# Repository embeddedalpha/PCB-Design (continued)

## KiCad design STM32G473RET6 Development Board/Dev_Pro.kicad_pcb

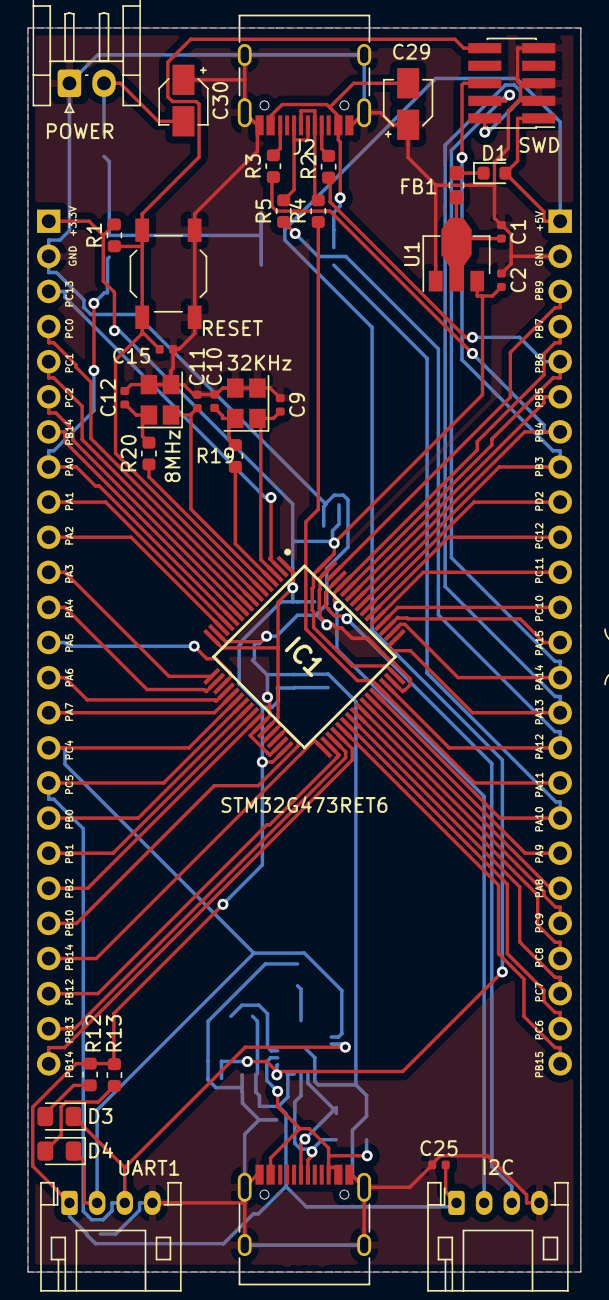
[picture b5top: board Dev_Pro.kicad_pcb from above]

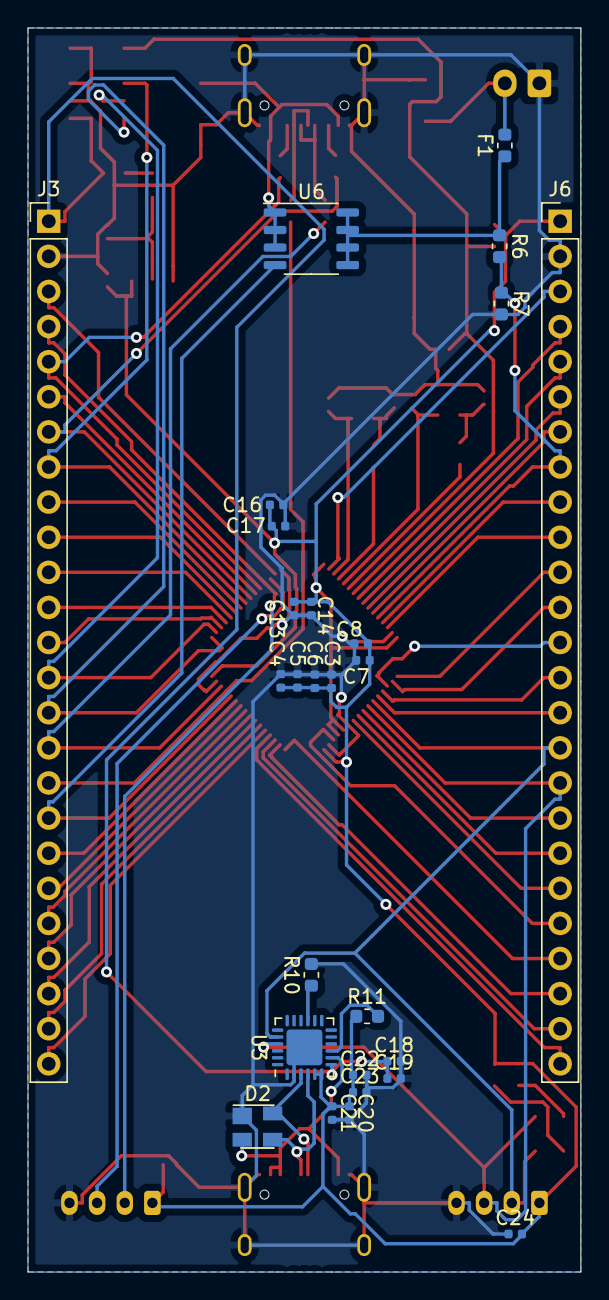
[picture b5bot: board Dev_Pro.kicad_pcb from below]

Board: 2 copper layers, 40.0 x 90.0 mm, 61 parts (27 on the bottom side), 73 nets.

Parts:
8MHz, 32KHz: Crystal_GND23; Crystal_SMD_SeikoEpson_FA238-4Pin_3.2x2.5mm
C1, C2, C24, C25: C_Small; C_0402_1005Metric
C3, C7, C13, C16, C18, C20, C22: 4.7U; C_0402_1005Metric
C4, C5, C6, C8, C9, C10, C11, C12, C14, C15, C17: 100N; C_0402_1005Metric
C19, C21, C23: 0.1U; C_0402_1005Metric
C29, C30: C; CP_Elec_3x5.3
D1: D_Schottky; D_0603_1608Metric
D2: SP0503BAHT; SOT-143
D3, D4: LED; LED_0805_2012Metric_Pad1.15x1.40mm_HandSolder
F1: Fuse; Fuse_0603_1608Metric
FB1: Ferrite_Bead; L_0603_1608Metric_Pad1.05x0.95mm_HandSolder
I2C: Conn_01x04; JST_PH_S4B-PH-K_1x04_P2.00mm_Horizontal
IC1: STM32G473RET6; QFP50P1200X1200X160-64N_STM32G473RET6
J1: Screw_Terminal_01x02; JST_EH_S2B-EH_1x02_P2.50mm_Horizontal
J2: USB_C_Receptacle_USB2.0; USB_C_Receptacle_HRO_TYPE-C-31-M-12
J3, J6: Conn_01x25; PinHeader_1x25_P2.54mm_Vertical
P1: USB_C_Plug_USB2.0; USB_C_Receptacle_HRO_TYPE-C-31-M-12
R1, R2, R3, R4, R5, R6, R7, R19, R20: R_Small; R_0603_1608Metric
R10, R11, R12, R13: 1K; R_0603_1608Metric
RESET: SW_SPST; SW_SPST_TL3342
SWD: Conn_ARM_JTAG_SWD_10; PinHeader_2x05_P1.27mm_Vertical_SMD
U1: AP2127R-3.3; SOT-89-3
U3: CP2102N-A01-GQFN24; QFN-24-1EP_4x4mm_P0.5mm_EP2.6x2.6mm
U6: IRF7205TRPB; SOP-8_3.9x4.9mm_P1.27mm
UART1: Conn_01x04; JST_PH_S4B-PH-K_1x04_P2.00mm_Horizontal

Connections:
+3.3V: C2.1, C3.1, C4.1, C5.1, C6.1, C7.1, C8.1, C13.1, C14.1, C16.1, C17.1, C20.1, C21.1, C22.1, C23.1, C24.2, C25.2, I2C.1, IC1.1, IC1.16, IC1.28, IC1.29, IC1.32, IC1.48, IC1.64, J6.1, R1.2, R11.1, R12.1, R13.1, U1.3, U3.5, U3.6, UART1.1
+5V: C18.1, C19.1, D1.2, J3.1, SWD.1, U3.7
/MCU/OSC8_IN: 8MHz.1, C11.1, IC1.5
/MCU/OSC8_OUT: IC1.6, R20.1
/MCU/OSC32_IN: 32KHz.1, C9.1, IC1.3
/MCU/OSC32_OUT: IC1.4, R19.1
/USB Power Delivery/DA+: J2.A6, J2.B6, R5.2
/USB Power Delivery/DA-: J2.A7, J2.B7, R4.2
/USB_to_UART/D+: D2.4, P1.A6, U3.3
/USB_to_UART/D-: D2.3, P1.A7, U3.4
GND: 8MHz.2, 8MHz.3, 32KHz.2, 32KHz.3, C1.2, C2.2, C3.2, C4.2, C5.2, C6.2, C7.2, C8.2, C9.2, C10.2, C11.2, C12.2, C13.2, C14.2, C15.1, C16.2, C17.2, C18.2, C19.2, C20.2, C21.2, C22.2, C23.2, C24.1, C25.1, C29.1, C30.1, D2.1, I2C.4, IC1.15, IC1.27, IC1.31, IC1.47, IC1.63, J1.1, J2.A1, J2.A12, J2.B1, J2.B12, J2.S1, J3.2, J6.2, P1.A1, P1.A12, P1.B1, P1.B12, P1.S1, R7.2, R10.2, RESET.2, SWD.3, SWD.5, SWD.9, U1.1, U3.2, U3.25, UART1.4
NRST: C15.2, IC1.7, R1.1, RESET.1, SWD.10
unnamed: C1.1, FB1.1, U1.2
unnamed: 32KHz.4, C10.1, R19.2
unnamed: 8MHz.4, C12.1, R20.2
unnamed: C29.2, J2.A4, J2.A9, J2.B4, J2.B9, U6.1, U6.2, U6.3
unnamed: C30.2, F1.2, J1.2
unnamed: D1.1, FB1.2
unnamed: D2.2, P1.A4, P1.A9, P1.B4, P1.B5, P1.B9, U3.8
unnamed: D3.2, R12.2
unnamed: D4.2, R13.2
unnamed: F1.1, R6.1, U6.5, U6.6, U6.7, U6.8
unnamed: J2.A5, R2.2
unnamed: J2.B5, R3.2
unnamed: R10.1, U3.15
unnamed: R11.2, U3.9
PA0: IC1.12, J6.8, R6.2, R7.1
PA1: IC1.13, J6.9
PA2: IC1.14, J6.10
PA3: IC1.17, J6.11
PA4: IC1.18, J6.12
PA5: IC1.19, J6.13
PA6: IC1.20, J6.14
PA7: IC1.21, J6.15
PA8: IC1.42, J3.20
PA9: IC1.43, J3.19
PA10: IC1.44, J3.18, U6.4
PA11: IC1.45, J3.17, R4.1
PA12: IC1.46, J3.16, R5.1
PA13: IC1.49, J3.15, SWD.2
PA14: IC1.50, J3.14, SWD.4
PA15: IC1.51, J3.13
PB0: IC1.24, J6.18
PB1: IC1.25, J6.19
PB2: IC1.26, J6.20
PB3: IC1.56, J3.8, SWD.6
PB4: IC1.57, J3.7, R3.1
PB5: IC1.58, J3.6
PB6: IC1.59, J3.5, R2.1
PB7: I2C.2, IC1.60, J3.4
PB8: I2C.3, IC1.61
PB9: IC1.62, J3.3
PB10: IC1.30, J6.21
PB11: IC1.33, J6.22
PB12: IC1.34, J6.23
PB13: IC1.35, J6.24
PB14: IC1.36, J6.25
PB15: IC1.37, J3.25
PC0: IC1.8, J6.4
PC1: IC1.9, J6.5
PC2: IC1.10, J6.6
PC3: IC1.11, J6.7
PC4: D4.1, IC1.22, J6.16, U3.20, UART1.2
PC5: D3.1, IC1.23, J6.17, U3.21, UART1.3
PC6: IC1.38, J3.24
PC7: IC1.39, J3.23
PC8: IC1.40, J3.22
PC9: IC1.41, J3.21
PC10: IC1.52, J3.12
PC11: IC1.53, J3.11
PC12: IC1.54, J3.10
PC13: IC1.2, J6.3
PD2: IC1.55, J3.9
